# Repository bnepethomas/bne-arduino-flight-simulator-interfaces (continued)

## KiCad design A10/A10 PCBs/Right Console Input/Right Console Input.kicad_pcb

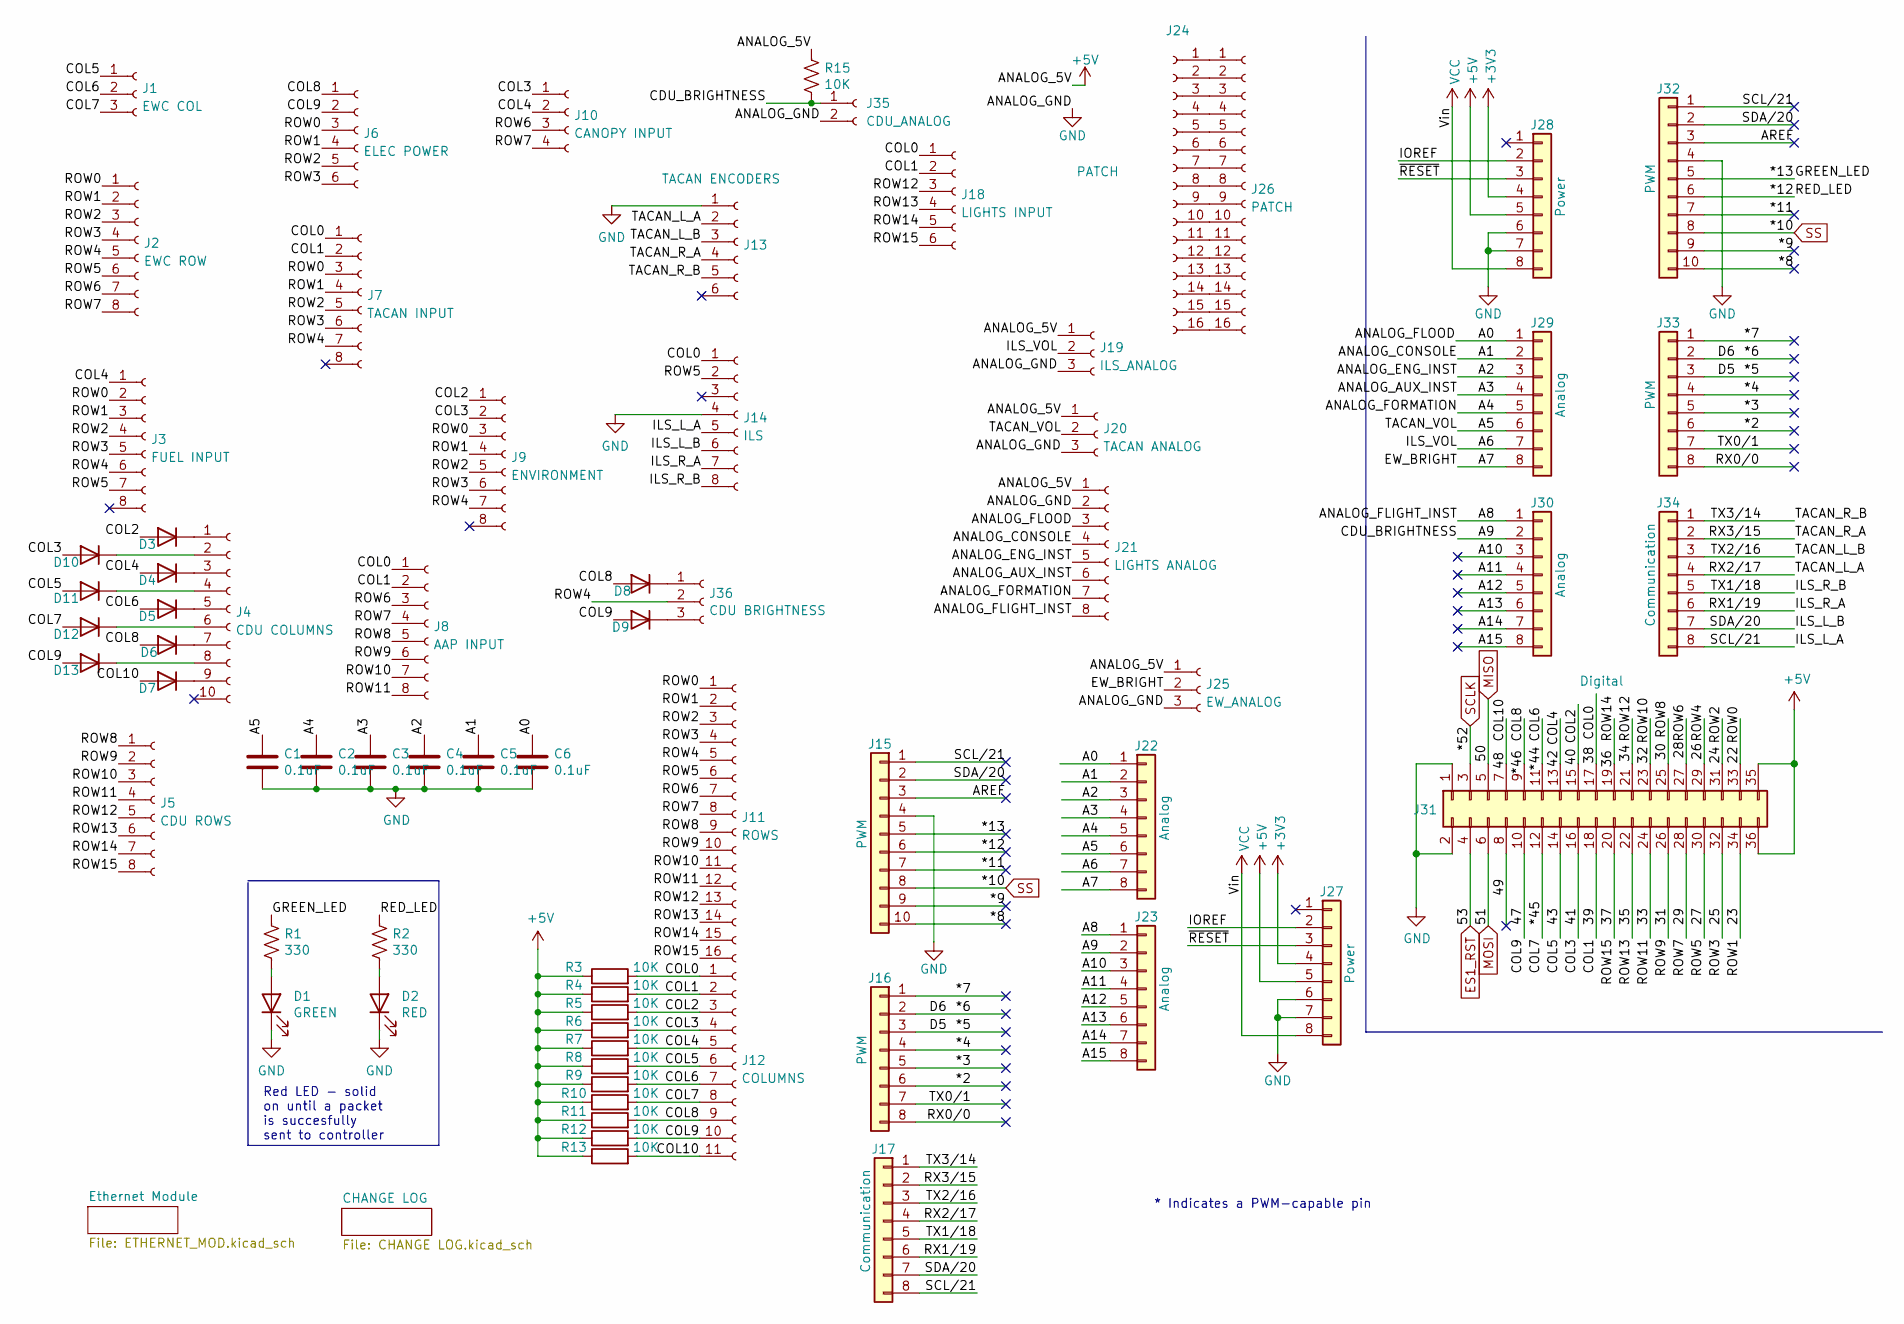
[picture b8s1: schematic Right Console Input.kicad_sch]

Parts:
C1, C2, C3, C4, C5, C6: 0.1uF; C_Disc_D6.0mm_W2.5mm_P5.00mm
D1: GREEN; LED_D3.0mm
D2: RED; LED_D3.0mm
D3, D4, D5, D6, D7, D8, D9, D10, D11, D12, D13: D; D_A-405_P2.54mm_Vertical_AnodeUp
J1: EWC COL; Molex_KK-254_AE-6410-03A_1x03_P2.54mm_Vertical
J2: EWC ROW; Molex_KK-254_AE-6410-08A_1x08_P2.54mm_Vertical
J3: FUEL INPUT; Molex_KK-254_AE-6410-08A_1x08_P2.54mm_Vertical
J4: CDU COLUMNS; Molex_KK-254_AE-6410-10A_1x10_P2.54mm_Vertical
J5: CDU ROWS; Molex_KK-254_AE-6410-08A_1x08_P2.54mm_Vertical
J6: ELEC POWER; Molex_KK-254_AE-6410-06A_1x06_P2.54mm_Vertical
J7: TACAN INPUT; Molex_KK-254_AE-6410-08A_1x08_P2.54mm_Vertical
J8: AAP INPUT; Molex_KK-254_AE-6410-08A_1x08_P2.54mm_Vertical
J9: ENVIRONMENT; Molex_KK-254_AE-6410-08A_1x08_P2.54mm_Vertical
J10: CANOPY INPUT; Molex_KK-254_AE-6410-04A_1x04_P2.54mm_Vertical
J11: ROWS; PinHeader_1x16_P2.54mm_Vertical
J12: COLUMNS; PinHeader_1x11_P2.54mm_Vertical
J13: TACAN ENCODERS; Molex_KK-254_AE-6410-06A_1x06_P2.54mm_Vertical
J14: ILS; Molex_KK-254_AE-6410-08A_1x08_P2.54mm_Vertical
J15, J32: PWM; PinSocket_1x10_P2.54mm_Vertical
J16, J33: PWM; PinSocket_1x08_P2.54mm_Vertical
J17, J34: Communication; PinSocket_1x08_P2.54mm_Vertical
J18: LIGHTS INPUT; Molex_KK-254_AE-6410-06A_1x06_P2.54mm_Vertical
J19: ILS_ANALOG; Molex_KK-254_AE-6410-03A_1x03_P2.54mm_Vertical
J20: TACAN ANALOG; Molex_KK-254_AE-6410-03A_1x03_P2.54mm_Vertical
J21: LIGHTS ANALOG; Molex_KK-254_AE-6410-08A_1x08_P2.54mm_Vertical
J22, J23, J29, J30: Analog; PinSocket_1x08_P2.54mm_Vertical
J24, J26: PATCH; PinHeader_1x16_P2.54mm_Vertical
J25: EW_ANALOG; Molex_KK-254_AE-6410-03A_1x03_P2.54mm_Vertical
J27, J28: Power; PinSocket_1x08_P2.54mm_Vertical
J31: Digital; PinSocket_2x18_P2.54mm_Vertical
J35: CDU_ANALOG; Molex_KK-254_AE-6410-02A_1x02_P2.54mm_Vertical
J36: CDU BRIGHTNESS; Molex_KK-254_AE-6410-03A_1x03_P2.54mm_Vertical
R1, R2: 330; R_Axial_DIN0204_L3.6mm_D1.6mm_P2.54mm_Vertical
R3, R4, R5, R6, R7, R8, R9, R10, R11, R12, R13, R15: 10K; R_Axial_DIN0204_L3.6mm_D1.6mm_P2.54mm_Vertical

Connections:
+3V3: J27.4, J28.4; also elsewhere on the board
+5V: J19.1, J20.1, J21.1, J25.1, J27.5, J28.5, J31.35, J31.36, R3.1, R4.1, R5.1, R6.1, R7.1, R8.1, R9.1, R10.1, R11.1, R12.1, R13.1, R15.1
/22: J2.1, J3.2, J6.3, J7.3, J9.3, J11.1, J31.33
/23: J2.2, J3.3, J6.4, J7.4, J9.4, J11.2, J31.34
/24: J2.3, J3.4, J6.5, J7.5, J9.5, J11.3, J31.31
/25: J2.4, J3.5, J6.6, J7.6, J9.6, J11.4, J31.32
/26: J2.5, J3.6, J7.7, J9.7, J11.5, J31.29, J36.2
/27: J2.6, J3.7, J11.6, J14.2, J31.30
/28: J2.7, J8.3, J10.3, J11.7, J31.27
/29: J2.8, J8.4, J10.4, J11.8, J31.28
/30: J5.1, J8.5, J11.9, J31.25
/31: J5.2, J8.6, J11.10, J31.26
/32: J5.3, J8.7, J11.11, J31.23
/33: J5.4, J8.8, J11.12, J31.24
/34: J5.5, J11.13, J18.3, J31.21
/35: J5.6, J11.14, J18.4, J31.22
/36: J5.7, J11.15, J18.5, J31.19
/37: J5.8, J11.16, J18.6, J31.20
/38: J7.1, J8.1, J12.1, J14.1, J18.1, J31.17, R3.2
/39: J7.2, J8.2, J12.2, J18.2, J31.18, R4.2
/40: D3.2 (A), J9.1, J12.3, J31.15, R5.2
/41: D10.2 (A), J9.2, J10.1, J12.4, J31.16, R6.2
/42: D4.2 (A), J3.1, J10.2, J12.5, J31.13, R7.2
/43: D11.2 (A), J1.1, J12.6, J31.14, R8.2
/47: D9.2 (A), D13.2 (A), J6.2, J12.10, J31.10, R12.2
/48: D7.2 (A), J12.11, J31.7, R13.2
/49: J31.8
/*2: J16.6, J33.6
/*3: J16.5, J33.5
/*4: J16.4, J33.4
/*5: J16.3, J33.3
/*6: J16.2, J33.2
/*7: J16.1, J33.1
/*8: J15.10, J32.10
/*9: J15.9, J32.9
/*11: J15.7, J32.7
/*12: J15.6, J32.6, R2.1
/*13: J15.5, J32.5, R1.1
/*44: D5.2 (A), J1.2, J12.7, J31.11, R9.2
/*45: D12.2 (A), J1.3, J12.8, J31.12, R10.2
/*46: D6.2 (A), D8.2 (A), J6.1, J12.9, J31.9, R11.2
/A0: C6.1, J21.3, J22.1, J29.1
/A1: C5.1, J21.4, J22.2, J29.2
/A2: C4.1, J21.5, J22.3, J29.3
/A3: C3.1, J21.6, J22.4, J29.4
/A4: C2.1, J21.7, J22.5, J29.5
/A5: C1.1, J20.2, J22.6, J29.6
/A6: J19.2, J22.7, J29.7
/A7: J22.8, J25.2, J29.8
/A8: J21.8, J23.1, J30.1
/A9: J23.2, J30.2, J35.1, R15.2
/A10: J23.3, J30.3
/A11: J23.4, J30.4
/A12: J23.5, J30.5
/A13: J23.6, J30.6
/A14: J23.7, J30.7
/A15: J23.8, J30.8
/AREF: J15.3, J32.3
/ILS_L_A: J14.5, J15.1, J17.8, J32.1, J34.8
/ILS_L_B: J14.6, J15.2, J17.7, J32.2, J34.7
/ILS_R_A: J14.7, J17.6, J34.6
/ILS_R_B: J14.8, J17.5, J34.5
/IOREF: J27.2, J28.2
/RX0/0: J16.8, J33.8
/RX2/17: J13.2, J17.4, J34.4
/RX3/15: J13.4, J17.2, J34.2
/TACAN_L_B: J13.3, J17.3, J34.3
/TACAN_R_B: J13.5, J17.1, J34.1
/TX0/1: J16.7, J33.7
/~RESET: J27.3, J28.3
ES1_RST: J31.4; also elsewhere on the board
GND: C1.2, C2.2, C3.2, C4.2, C5.2, C6.2, D1.1 (K), D2.1 (K), J13.1, J14.4, J15.4, J19.3, J20.3, J21.2, J25.3, J27.6, J27.7, J28.6, J28.7, J31.1, J31.2, J32.4, J35.2; also elsewhere on the board
MISO: J31.5; also elsewhere on the board
MOSI: J31.6; also elsewhere on the board
unnamed: D1.2 (A), R1.2
unnamed: D2.2 (A), R2.2
unnamed: D3.1 (K), J4.1
unnamed: D4.1 (K), J4.3
unnamed: D5.1 (K), J4.5
unnamed: D6.1 (K), J4.7
unnamed: D7.1 (K), J4.9
unnamed: D8.1 (K), J36.1
unnamed: D9.1 (K), J36.3
unnamed: D10.1 (K), J4.2
unnamed: D11.1 (K), J4.4
unnamed: D12.1 (K), J4.6
unnamed: D13.1 (K), J4.8
unnamed: J24.1, J26.1
unnamed: J24.2, J26.2
unnamed: J24.3, J26.3
unnamed: J24.4, J26.4
unnamed: J24.5, J26.5
unnamed: J24.6, J26.6
unnamed: J24.7, J26.7
unnamed: J24.8, J26.8
unnamed: J24.9, J26.9
unnamed: J24.10, J26.10
unnamed: J24.11, J26.11
unnamed: J24.12, J26.12
unnamed: J24.13, J26.13
unnamed: J24.14, J26.14
unnamed: J24.15, J26.15
unnamed: J24.16, J26.16
SCLK: J31.3; also elsewhere on the board
SS: J15.8, J32.8; also elsewhere on the board
VCC: J27.8, J28.8

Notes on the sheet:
Red LED - solid on until a packet is succesfully sent to controller
* Indicates a PWM-capable pin

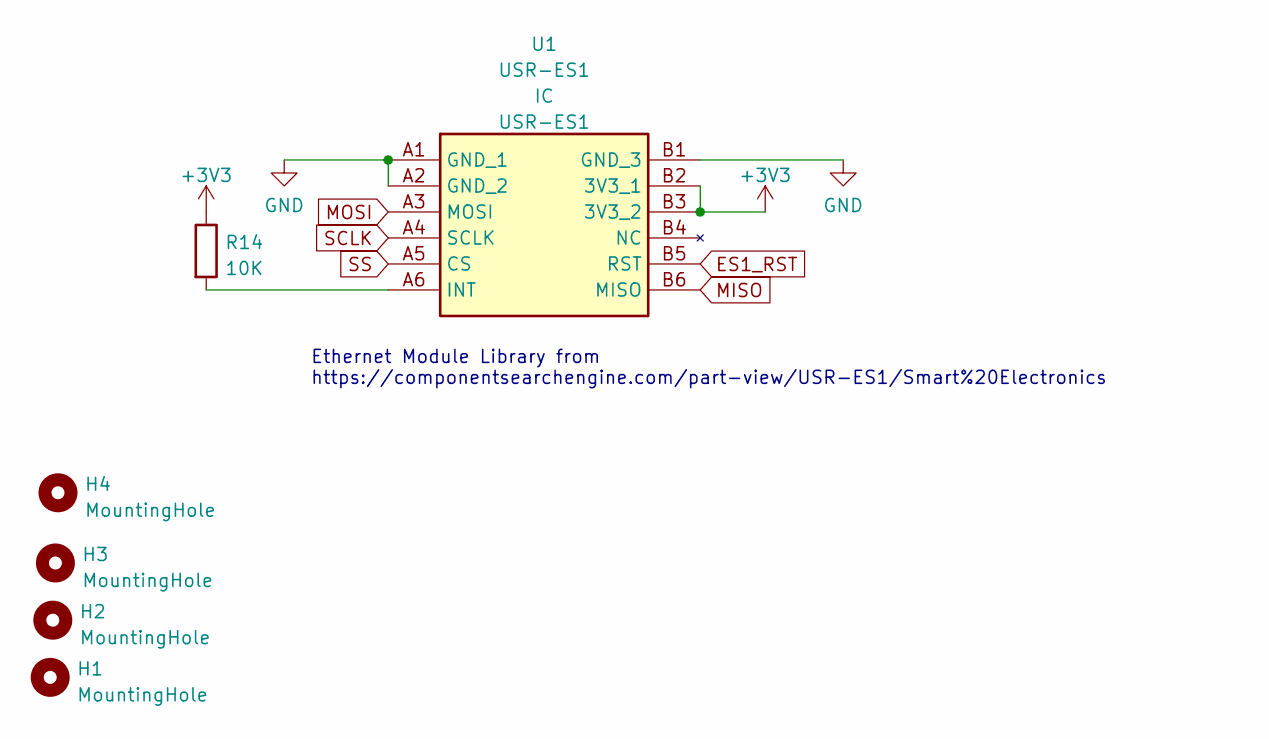
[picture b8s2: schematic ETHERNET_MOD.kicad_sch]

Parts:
H1, H2, H3, H4: MountingHole; MountingHole_3.2mm
R14: 10K; R_Axial_DIN0204_L3.6mm_D1.6mm_P2.54mm_Vertical
U1: USR-ES1; USRES1; Manufacturer_Part_Number USR-ES1

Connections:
+3V3: R14.1, U1.B2 (3V3_1), U1.B3 (3V3_2); also elsewhere on the board
ES1_RST: U1.B5 (RST); also elsewhere on the board
GND: U1.A1 (GND_1), U1.A2 (GND_2), U1.B1 (GND_3); also elsewhere on the board
MISO: U1.B6 (MISO); also elsewhere on the board
MOSI: U1.A3 (MOSI); also elsewhere on the board
unnamed: R14.2, U1.A6 (INT)
SCLK: U1.A4 (SCLK); also elsewhere on the board
SS: U1.A5 (CS); also elsewhere on the board

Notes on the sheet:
Ethernet Module Library from https://componentsearchengine.com/part-view/USR-ES1/Smart%20Electronics

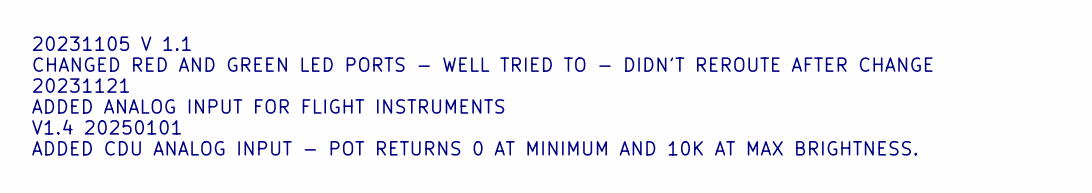
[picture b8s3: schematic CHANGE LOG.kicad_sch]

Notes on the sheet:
20231105 V 1.1 CHANGED RED AND GREEN LED PORTS - WELL TRIED TO - DIDN'T REROUTE AFTER CHANGE 20231121 ADDED ANALOG INPUT FOR FLIGHT INSTRUMENTS V1.4 20250101 ADDED CDU ANALOG INPUT - POT RETURNS 0 AT MINIMUM AND 10K AT MAX BRIGHTNESS.

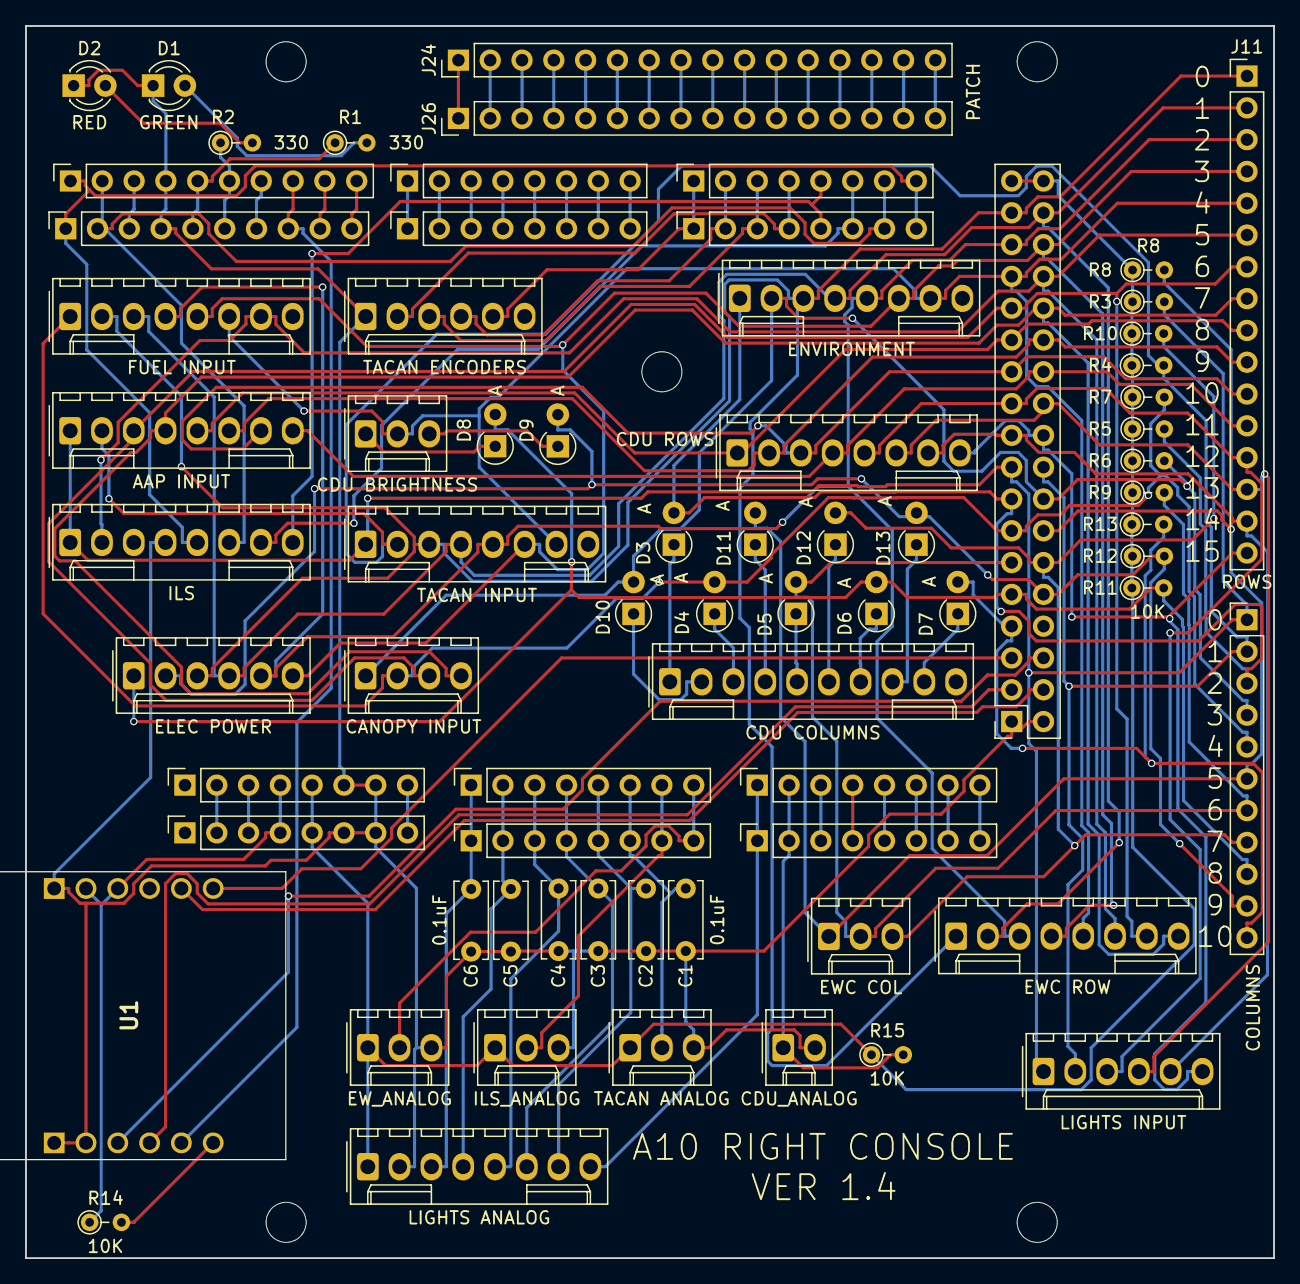
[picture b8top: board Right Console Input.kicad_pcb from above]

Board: 2 copper layers, 99.7 x 98.4 mm, 76 parts (0 on the bottom side), 106 nets.

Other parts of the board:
MH1: MountingHole_3.2mm
